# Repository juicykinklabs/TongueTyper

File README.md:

# TongueTyper

A reinvented talking-gag platform with WiFi control, USB output, accelerometer, speaker, and haptic feedback.

## ⚠️ Pre-release
This repo is still missing a lot of documentation, and there are no releases at this time.
Feel free to take a look around though.

We're considering swapping to [this](https://a.co/d/01ACvRYG) module that combines the ESP32, display, and accelerometer, and has a BMS. It would still require a PCB for SD, audio, and the buttons/GPIO expander.

## Directory

 - GWR-firmware: ESP32-S3 firmware (platformio, arduinoespressif32)
 - PCB: printed circuit board design files (KiCAD)
 - SD-Media: SD Card files and helper scripts
    - Additional emojis may be found: https://www.emojiall.com/en/image-emoji-platform/apple/hd
 - TT-Models: 3D printable and silicone parts

## Footer

AI Use Policy: Discouraged, and ONLY allowed for one-off helper scripts. Any files generated by artificial intelligence begin with AI_* and should be reviewed and rewritten by a human. Please do not include this code in the training of any AI model.

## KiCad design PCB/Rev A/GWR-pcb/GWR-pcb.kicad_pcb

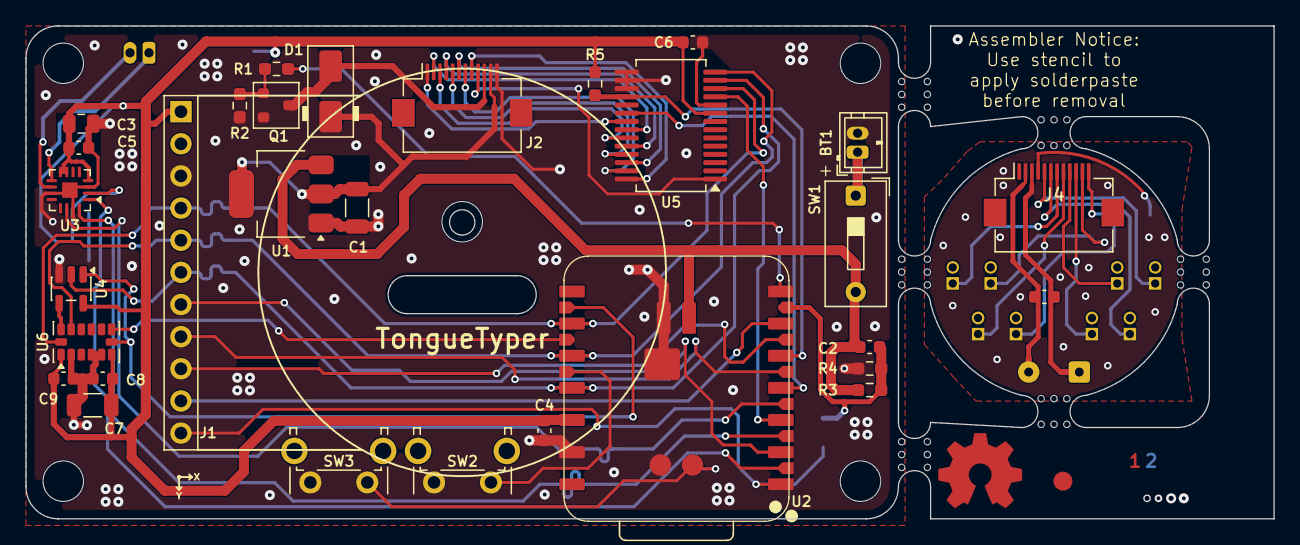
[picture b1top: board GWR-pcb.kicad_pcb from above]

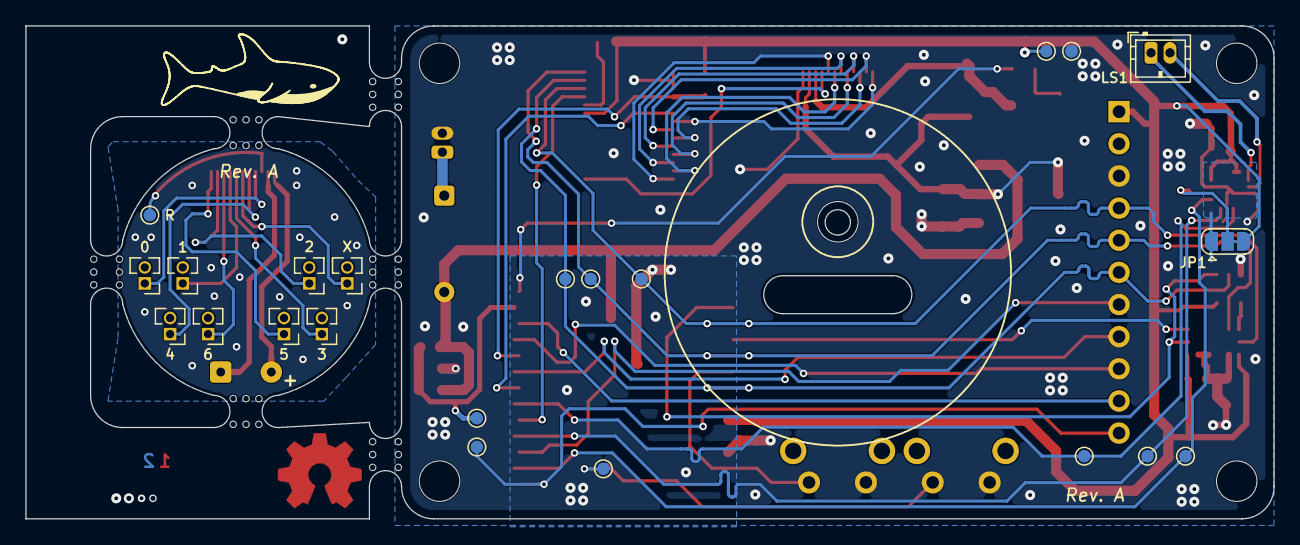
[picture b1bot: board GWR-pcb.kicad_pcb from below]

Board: 2 copper layers, 98.6 x 39.0 mm, 58 parts (23 on the bottom side), 41 nets.

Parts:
BT1: Battery_Cell; JST_ZH_B2B-ZR_1x02_P1.50mm_Vertical
C1, C7: 10u; C_1206_3216Metric
C2: 10n; C_0603_1608Metric
C3: 10u; C_0805_2012Metric
C4: 1u; C_0603_1608Metric
C5, C6, C8, C9: 100n; C_0603_1608Metric
C10: TBD; C_0603_1608Metric
D1: S1A; D_SMA
H1, H2, H3, H4, H5: MountingHole; MountingHole_3.2mm_M3_DIN965
J1: Conn_01x11; Adafruit_128RoundTFT
J2, J4: Conn_01x12; Hirose_FH12-12S-0.5SH_1x12-1MP_P0.50mm_Horizontal
J3: Conn_01x02; SolderWire-0.15sqmm_1x02_P4mm_D0.5mm_OD1.5mm
J5, J6, J7, J8, J9, J10, J11, J12: Conn_01x02; PinHeader_1x02_P1.27mm_Vertical
JP1: SolderJumper_3_Open; SolderJumper-3_P1.3mm_Open_RoundedPad1.0x1.5mm
LS1: Speaker; JST_ZH_B2B-ZR_1x02_P1.50mm_Vertical
Q1: AO3400A; SOT-23
R1: 220; R_0603_1608Metric_Pad0.98x0.95mm_HandSolder
R2: 100k; R_0603_1608Metric_Pad0.98x0.95mm_HandSolder
R3: 820k; R_0603_1608Metric_Pad0.98x0.95mm_HandSolder
R4: 270k; R_0603_1608Metric_Pad0.98x0.95mm_HandSolder
R5: 10k; R_0603_1608Metric_Pad0.98x0.95mm_HandSolder
SW1: SW_DIP_x01; SW_DIP_SPSTx01_Slide_9.78x4.72mm_W7.62mm_P2.54mm
SW2: Angled_Mode; SW_Tactile_SPST_Angled_PTS645Vx83-2LFS
SW3: Angled_RST; SW_Tactile_SPST_Angled_PTS645Vx83-2LFS
TP1: 3V3; TestPoint_Pad_D1.0mm
TP2: GND; TestPoint_Pad_D1.0mm
TP3: VBATDIV; TestPoint_Pad_D1.0mm
TP4: RST; TestPoint_Pad_D1.0mm
TP5: MOSI; TestPoint_Pad_D1.0mm
TP6: MISO; TestPoint_Pad_D1.0mm
TP7: SCK; TestPoint_Pad_D1.0mm
TP8: BLPWM; TestPoint_Pad_D1.0mm
TP9: DIN; TestPoint_Pad_D1.0mm
TP10: BCLK; TestPoint_Pad_D1.0mm
TP11: LRCLK; TestPoint_Pad_D1.0mm
TP12: RES; TestPoint_Pad_D1.0mm
U1: AMS1117-1.5; SOT-223-3_TabPin2
U2: XIAO-ESP32-S3-Plus-SMD
U3: MAX98357A; TQFN-16-1EP_3x3mm_P0.5mm_EP1.23x1.23mm
U4: 74AUP1G32; SOT-23-5
U5: MCP23S17x-x-SS; SSOP-28_5.3x10.2mm_P0.65mm
U6: ADXL343; LGA-14_3x5mm_P0.8mm_LayoutBorder1x6y

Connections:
+3V3: C3.1, C4.1, C5.1, C6.1, C7.1, C8.1, C9.1, J1.1, JP1.3 (B), R5.1, TP1.1 (1_1), U2.12 (3V3), U3.4 (~SD_MODE), U3.7 (VDD), U3.8 (VDD), U4.5 (VCC), U5.9 (V_{DD}), U6.1 (Vdd_I/O), U6.6 (Vs)
/ADXL_CS: U2.21 (GPIO11_DVP_Y8_SPI_MOSI1), U4.1, U6.7 (~CS)
/AUDIO_+: LS1.1, U3.9 (OUTP)
/AUDIO_-: LS1.2, U3.10 (OUTN)
/AUDIO_GAIN: JP1.2 (C), U3.2 (GAIN_SLOT)
/BUTTON_A: J2.1, J4.12, J5.1, U5.21 (GPA0)
/BUTTON_B: J2.2, J4.11, J6.1, U5.22 (GPA1)
/BUTTON_C: J2.3, J4.10, J7.1, U5.23 (GPA2)
/BUTTON_D: J2.4, J4.9, J8.1, U5.24 (GPA3)
/BUTTON_E: J2.5, J4.8, J9.1, U5.25 (GPA4)
/BUTTON_F: J2.6, J4.7, J10.1, U5.26 (GPA5)
/BUTTON_G: J2.7, J4.6, J11.1, U5.27 (GPA6)
/BUTTON_H: J2.8, J4.5, J12.1, U5.28 (GPA7)
/ESP_MISO: J1.5, TP6.1 (1_1), U2.10 (GPIO8_A9_D9_MISO), U5.14 (SO), U6.12 (SDO/ADDR)
/ESP_MOSI: J1.6, TP5.1 (1_1), U2.11 (GPIO9_A10_D10_MOSI), U4.2, U5.13 (SI)
/ESP_SCK: J1.4, TP7.1 (1_1), U2.9 (GPIO7_A8_D8_SCK), U5.12 (SCK), U6.14 (SCL/SCLK)
/GPIOEXP_CS: U2.3 (GPIO3_A2_D2), U5.11 (~CS)
/GPIOEXP_INTA: U2.4 (GPIO4_A3_D3), U5.20 (INTA)
/GPIOEXP_RST: R5.2, U2.5 (GPIO5_A4_D4_SDA), U5.18 (~RESET)
/I2S_BCLK: TP10.1 (1_1), U2.16 (GPIO39_CAM_SCL_I2S_SCK), U3.16 (BCLK)
/I2S_DIN: TP9.1 (1_1), U2.15 (GPIO38_DVP_VSYNC_I2S_SD), U3.1 (DIN)
/I2S_LRCLK: TP11.1 (1_1), U2.17 (GPIO40_CAM_SDA_I2S_WS), U3.14 (LRCLK)
/MOTOR_HIGH: C1.1, C10.1, D1.1 (K), J2.11, J3.2, J4.2, U1.2 (VO)
/MOTOR_LOW: C10.2, D1.2 (A), J2.10, J3.1, J4.3, Q1.3 (D)
/SD_CS: J1.10, U2.6 (GPIO6_A5_D5_SCL)
/SIG_ADXL_INT1: U2.22 (GPIO12_DVP_Y7_SPI_MISO1), U6.8 (INT1)
/SIG_QMOTOR: Q1.1 (G), R1.2, R2.1
/SIG_RESERVED1: J2.9, J4.4, TP12.1 (1_1), U5.1 (GPB0)
/SIG_SW_MODE: SW2.1 (A), U2.23 (GPIO13_DVP_PCLK_SPI_SCK1)
/SIG_SW_RST: SW3.1 (A), TP4.1 (1_1), U2.26 (EN)
/SIG_VIBRATION: R1.1, U2.7 (GPIO43_D6_TX)
/TFT_BL_PWM: J1.11, TP8.1 (1_1), U2.1 (GPIO1_A0_D0)
/TFT_CS: J1.7, U2.2 (GPIO2_A1_D1)
/TFT_DC: J1.9, U2.19 (GPIO42_PDM_CLK_TX1)
/TFT_RST: J1.8, U2.18 (GPIO41_PDM_DATA_RX1)
/VBAT: C2.1, R3.2, SW1.2, U1.3 (VI), U2.32 (VBAT)
/VBAT_DIVIDER: C2.2, R3.1, R4.2, TP3.1 (1_1), U2.20 (GPIO10_XMCLK_ADC_BAT)
GND: BT1.2 (-), C1.2, C3.2, C4.2, C5.2, C6.2, C7.2, C8.2, C9.2, J1.3, J2.12, JP1.1 (A), Q1.2 (S), R2.2, R4.1, SW2.2 (B), SW3.2 (B), TP2.1 (1_1), U1.1 (GND), U2.13 (GND), U2.27 (GND1), U2.33 (GND2), U2.34 (PAD), U3.3 (GND), U3.11 (GND), U3.15 (GND), U3.17 (PAD), U4.3 (GND), U5.10 (V_{SS}), U5.15 (A0), U5.16 (A1), U5.17 (A2), U6.2 (GND), U6.4 (GND), U6.5 (GND)
GND_DAUGHTER: J4.1, J5.2, J6.2, J7.2, J8.2, J9.2, J10.2, J11.2, J12.2
unnamed: BT1.1 (+), SW1.1
unnamed: U4.4, U6.13 (SDA/SDI/SDIO)

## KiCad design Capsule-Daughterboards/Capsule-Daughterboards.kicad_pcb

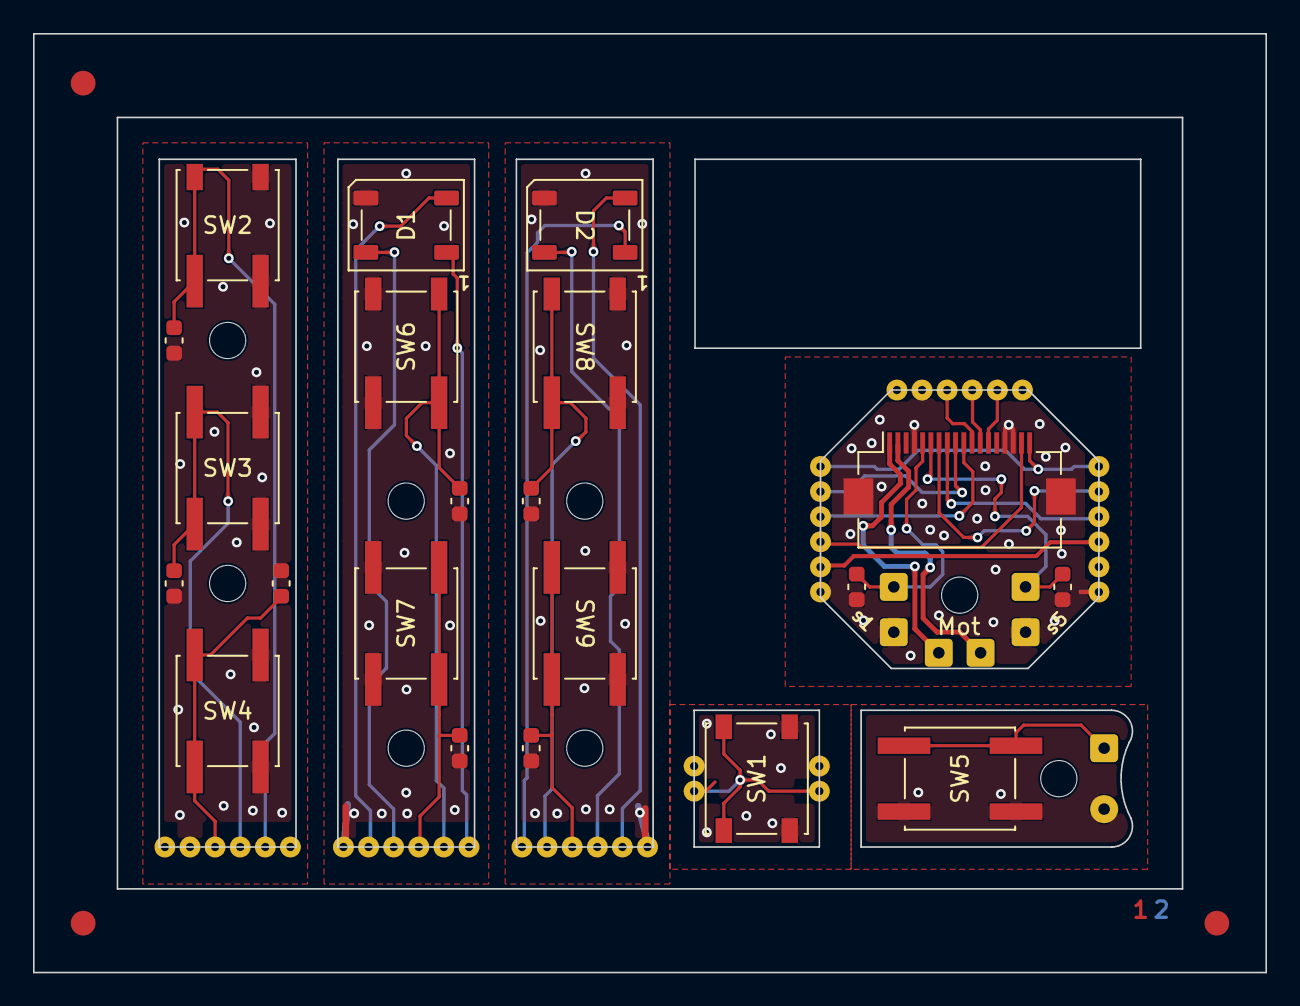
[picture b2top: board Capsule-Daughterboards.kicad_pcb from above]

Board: 2 copper layers, 74.8 x 57.0 mm, 47 parts (0 on the bottom side), 23 nets.

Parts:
C1, C2, C3, C4, C5, C6, C7, C8, C9: 10nF; C_0603_1608Metric
D1, D2: WS2812B; LED_WS2812B_PLCC4_5.0x5.0mm_P3.2mm
FID1, FID2, FID3: Fiducial; Fiducial_1.5mm_Mask3mm
H1, H2, H3, H4, H5, H6, H7, H8: MountingHole; MountingHole_2.2mm_M2_ISO14580
J1, J2, J3, J4, J8, J9: Conn_01x01; SolderWire-0.127sqmm_1x01_D0.48mm_OD1mm
J5: Edge Connection (Bottom); 1x6_SolderableEdgeConnector
J6: Edge Connection (Left); 1x6_SolderableEdgeConnector
J7: Edge Connection (Right); 1x6_SolderableEdgeConnector
J10: FFC; Hirose_FH12-18S-0.5SH_1x18-1MP_P0.50mm_Horizontal
J13, J15, J16, J17, J18: Edge Connection; 1x6_SolderableEdgeConnector
J14: Flywires; SolderWire-0.127sqmm_1x02_P3.7mm_D0.48mm_OD1mm
SW1, SW2, SW3, SW4, SW5, SW6, SW7, SW8, SW9: SW_Push; SW_SPST_EVQQ2

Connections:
+5V_Octo: J6.1, J7.6, J10.18
+5V_left: D1.1 (VDD), J15.6
+5V_right: D2.1 (VDD), J16.1
/MOTOR_HIGH: J8.1 (Pin_1_1), J10.1
/MOTOR_LOW: J9.1 (Pin_1_1), J10.2
DIN_left: D1.4 (DIN), J6.4, J10.17, J15.3
DIN_right: D1.2 (DOUT), D2.4 (DIN), J6.5, J7.3, J15.2, J16.4
DOUT_right: D2.2 (DOUT), J7.2, J16.5
GND_Octo: C1.2, C5.2, J2.1 (Pin_1_1), J4.1 (Pin_1_1), J5.5, J6.6, J7.1, J10.4, J10.15, J10.16, J10.MP (MountPin)
GND_bottom: C2.2, C3.2, C4.2, J13.2, SW2.2, SW3.2, SW4.2
GND_left: C6.2, C7.2, D1.3 (VSS), J15.1, SW6.2, SW7.2
GND_right: C8.2, C9.2, D2.3 (VSS), J16.6, SW8.2, SW9.2
GND_tip: J17.3, J18.3, SW1.2
GND_top: J14.2, SW5.2
SWITCH_1: C1.1, J1.1 (Pin_1_1), J10.5, J17.4, J18.4, SW1.1
SWITCH_2: C2.1, J5.2, J10.13, J13.5, SW2.1
SWITCH_3: C3.1, J5.3, J10.12, J13.4, SW3.1
SWITCH_4: C4.1, J5.4, J10.11, J13.3, SW4.1
SWITCH_5: C5.1, J3.1 (Pin_1_1), J10.6, J14.1, SW5.1
SWITCH_6: C6.1, J6.2, J10.9, J15.5, SW6.1
SWITCH_7: C7.1, J6.3, J10.10, J15.4, SW7.1
SWITCH_8: C8.1, J7.5, J10.7, J16.2, SW8.1
SWITCH_9: C9.1, J7.4, J10.8, J16.3, SW9.1

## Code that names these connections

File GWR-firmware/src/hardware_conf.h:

#pragma once

// project hardware description file

#include <Arduino.h>


// *** XIAO PINOUT HELPER ***
//          USB PORT
//   reset button  boot0 button
//   led pmic      led gpio21
//     GPIO1/D0     VBUS
//     GPIO2/D1     GND
//     GPIO3/D2     3V3 ldo out
//     GPIO4/D3     GPIO9/D10
//     GPIO5/D4     GPIO8/D9
//     GPIO6/D5     GPIO7/D8
//     GPIO43/D6    GPIO44/D7


#define TFT_DC D1
#define TFT_CS D2
//#define TFT_RST D3

#define XIAO_SCK D8
#define XIAO_MISO D9
#define XIAO_MOSI D10

#define I2S_BCLK D0 // Bit clock
#define I2S_LRC D3  // Word select (LR clock)
#define I2S_DOUT D6 // Data out to DAC

#define SD_CS D4
#define ADXL_CS D5

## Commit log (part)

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2026-06-16 upload all files
2026-06-16 add 3d model note
2026-06-16 add debug and cache
2026-06-17 keybinds prototype
2026-06-17 update info
2026-06-17 preliminary button inputs test
2026-06-17 update to use GPIO expander, minor fixes
2026-06-21 use scancodes for non-ascii characters
2026-06-21 update gitignores
2026-06-21 improvements (WIP)
2026-06-21 standardize port to match 3D; panelize daughterboard
2026-06-21 minor fixes
